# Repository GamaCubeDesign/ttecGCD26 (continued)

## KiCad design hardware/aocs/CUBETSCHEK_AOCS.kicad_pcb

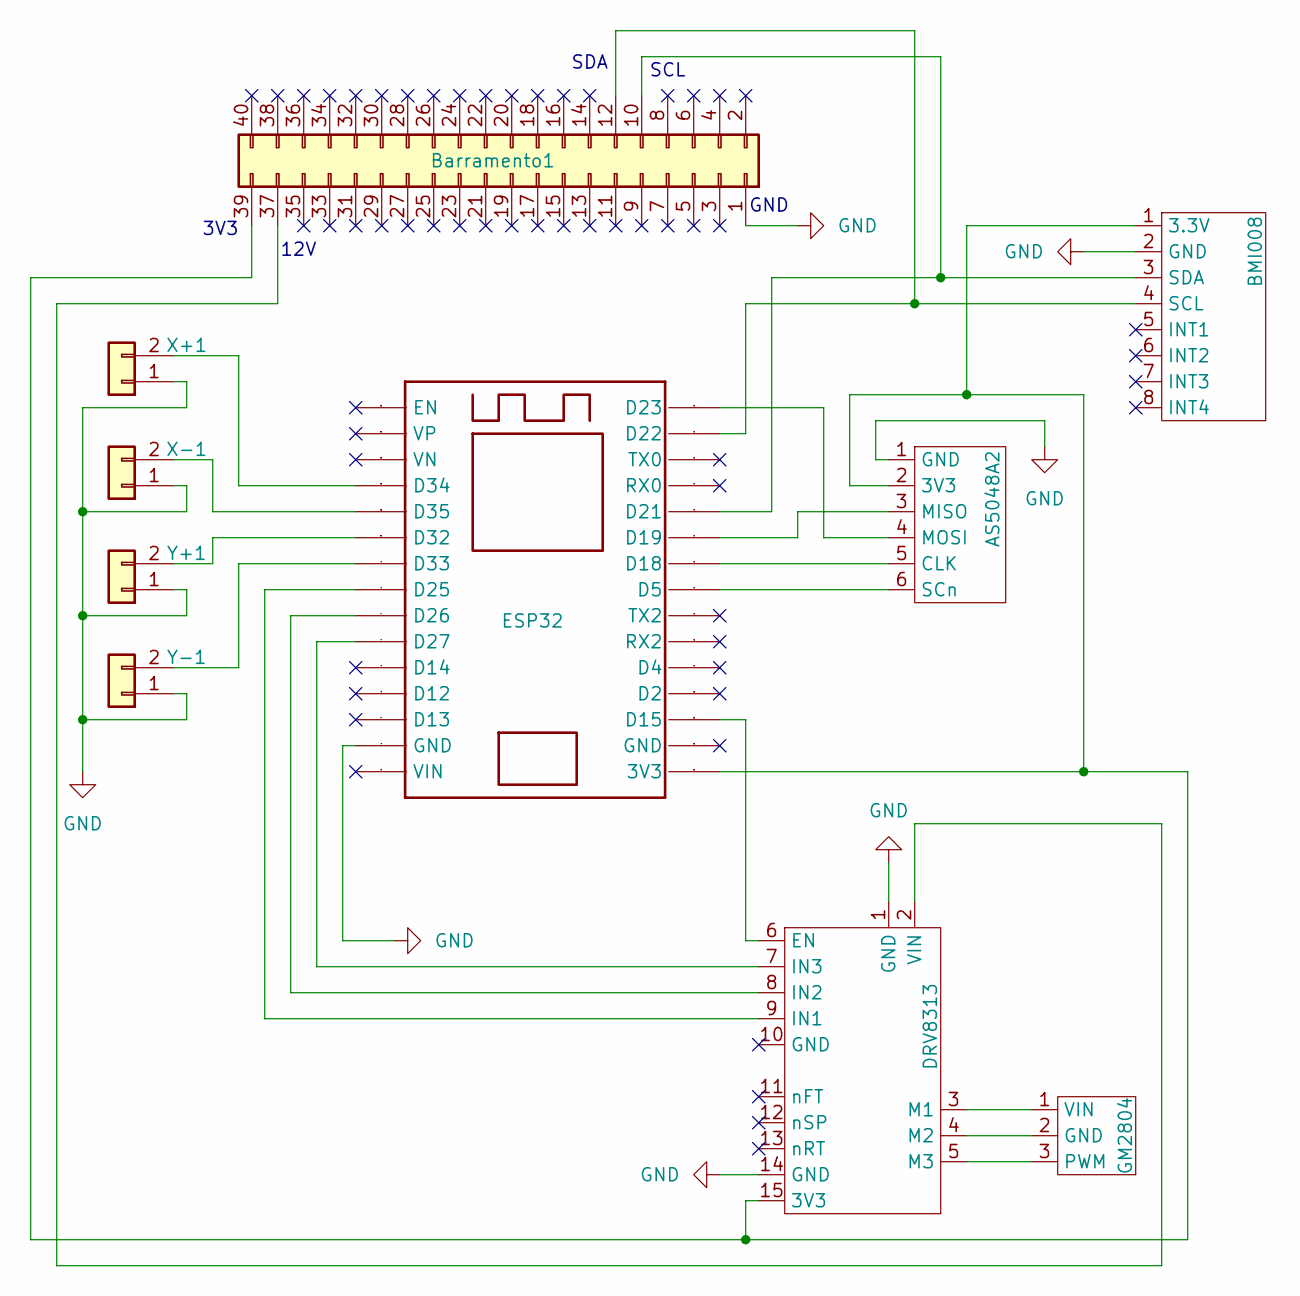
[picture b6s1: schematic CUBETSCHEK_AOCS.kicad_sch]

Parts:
AS5048A2: AS5048A
BMI008: BMI088
Barramento1: Barramento
DRV8313: DRV8313; DRV3813
ESP32: ESP32; ESP32-30p
GM2804: GM2804; GM2804_Molex_KK-3p-254
X+1: JST; JST_PLACA
X-1: JST; JST_PLACA
Y+1: JST; JST_PLACA
Y-1: JST; JST_PLACA

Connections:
GND: AS5048A2.1 (GND), BMI008.2 (GND), Barramento1.1, DRV8313.1 (GND), DRV8313.14 (GND), ESP32.2 (GND), X+1.1, X-1.1, Y+1.1, Y-1.1
unnamed: AS5048A2.2 (3V3), BMI008.1 (3.3V), Barramento1.39, DRV8313.15 (3V3), ESP32.16 (3V3)
unnamed: AS5048A2.5 (CLK), ESP32.24 (D18)
unnamed: AS5048A2.3 (MISO), ESP32.25 (D19)
unnamed: AS5048A2.4 (MOSI), ESP32.30 (D23)
unnamed: AS5048A2.6 (SCn), ESP32.23 (D5)
unnamed: BMI008.4 (SCL), Barramento1.12, ESP32.29 (D22)
unnamed: BMI008.3 (SDA), Barramento1.10, ESP32.26 (D21)
unnamed: Barramento1.37, DRV8313.2 (VIN)
unnamed: DRV8313.6 (EN), ESP32.18 (D15)
unnamed: DRV8313.9 (IN1), ESP32.8 (D25)
unnamed: DRV8313.8 (IN2), ESP32.7 (D26)
unnamed: DRV8313.7 (IN3), ESP32.6 (D27)
unnamed: DRV8313.3 (M1), GM2804.1 (VIN)
unnamed: DRV8313.4 (M2), GM2804.2 (GND)
unnamed: DRV8313.5 (M3), GM2804.3 (PWM)
unnamed: ESP32.10 (D32), Y+1.2
unnamed: ESP32.9 (D33), Y-1.2
unnamed: ESP32.12 (D34), X+1.2
unnamed: ESP32.11 (D35), X-1.2

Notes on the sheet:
GND
SDA
SCL
3V3
12V

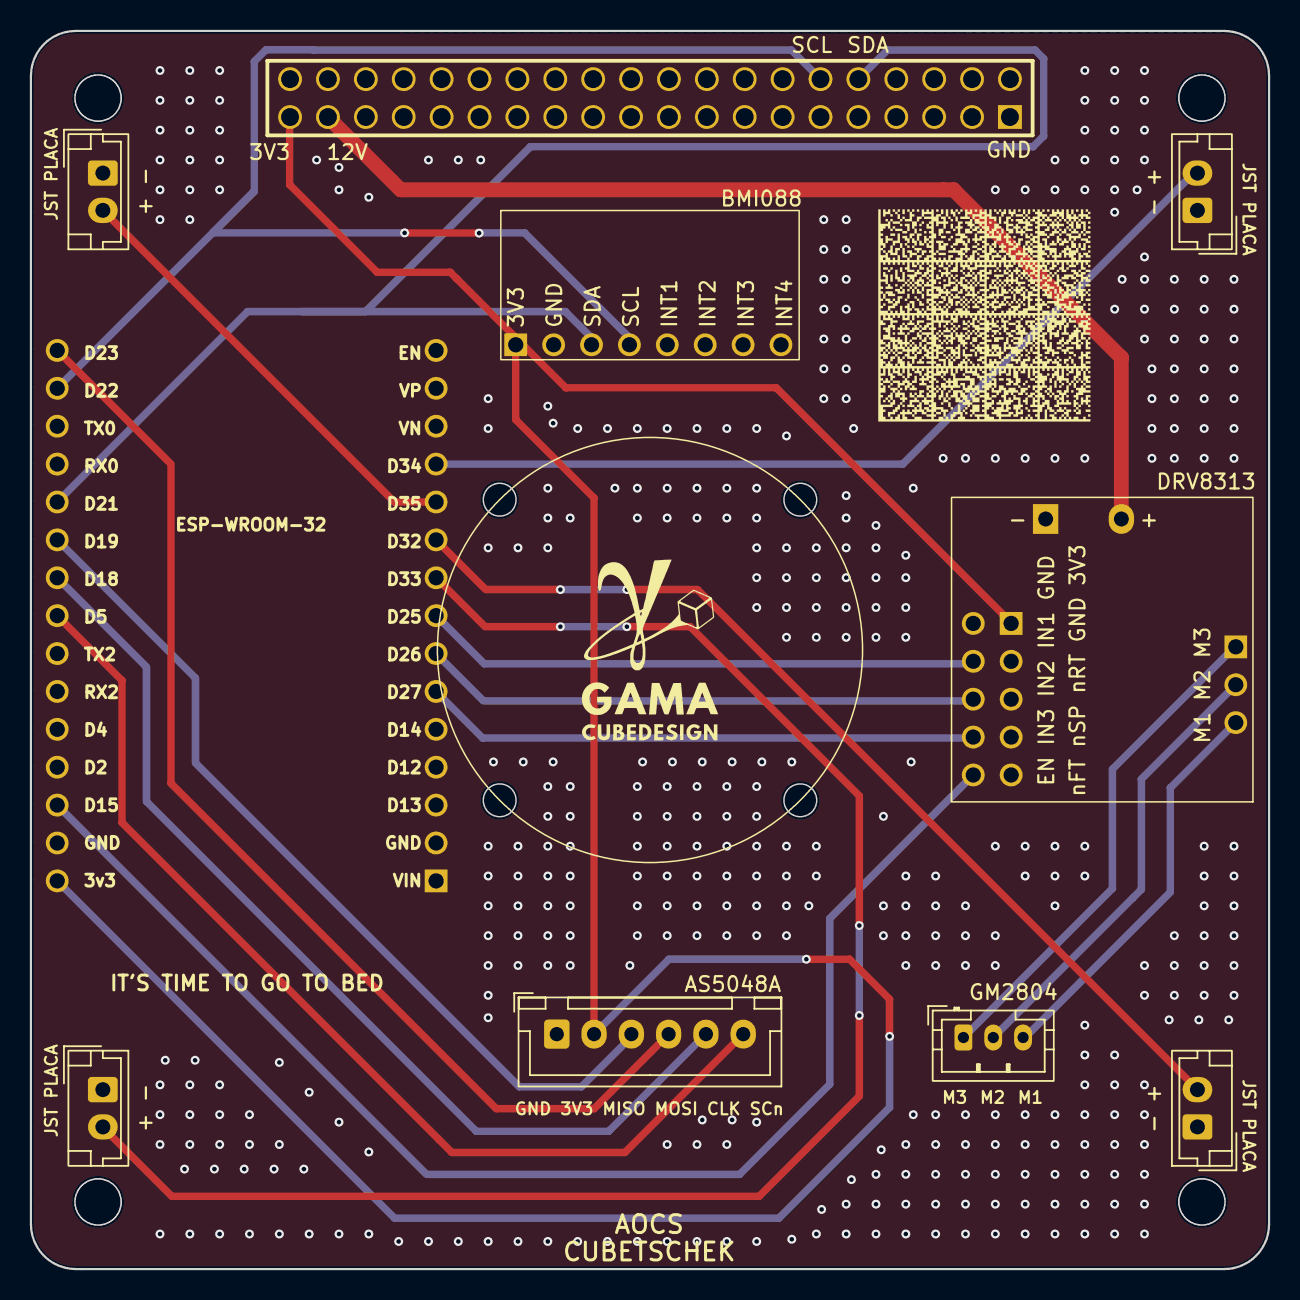
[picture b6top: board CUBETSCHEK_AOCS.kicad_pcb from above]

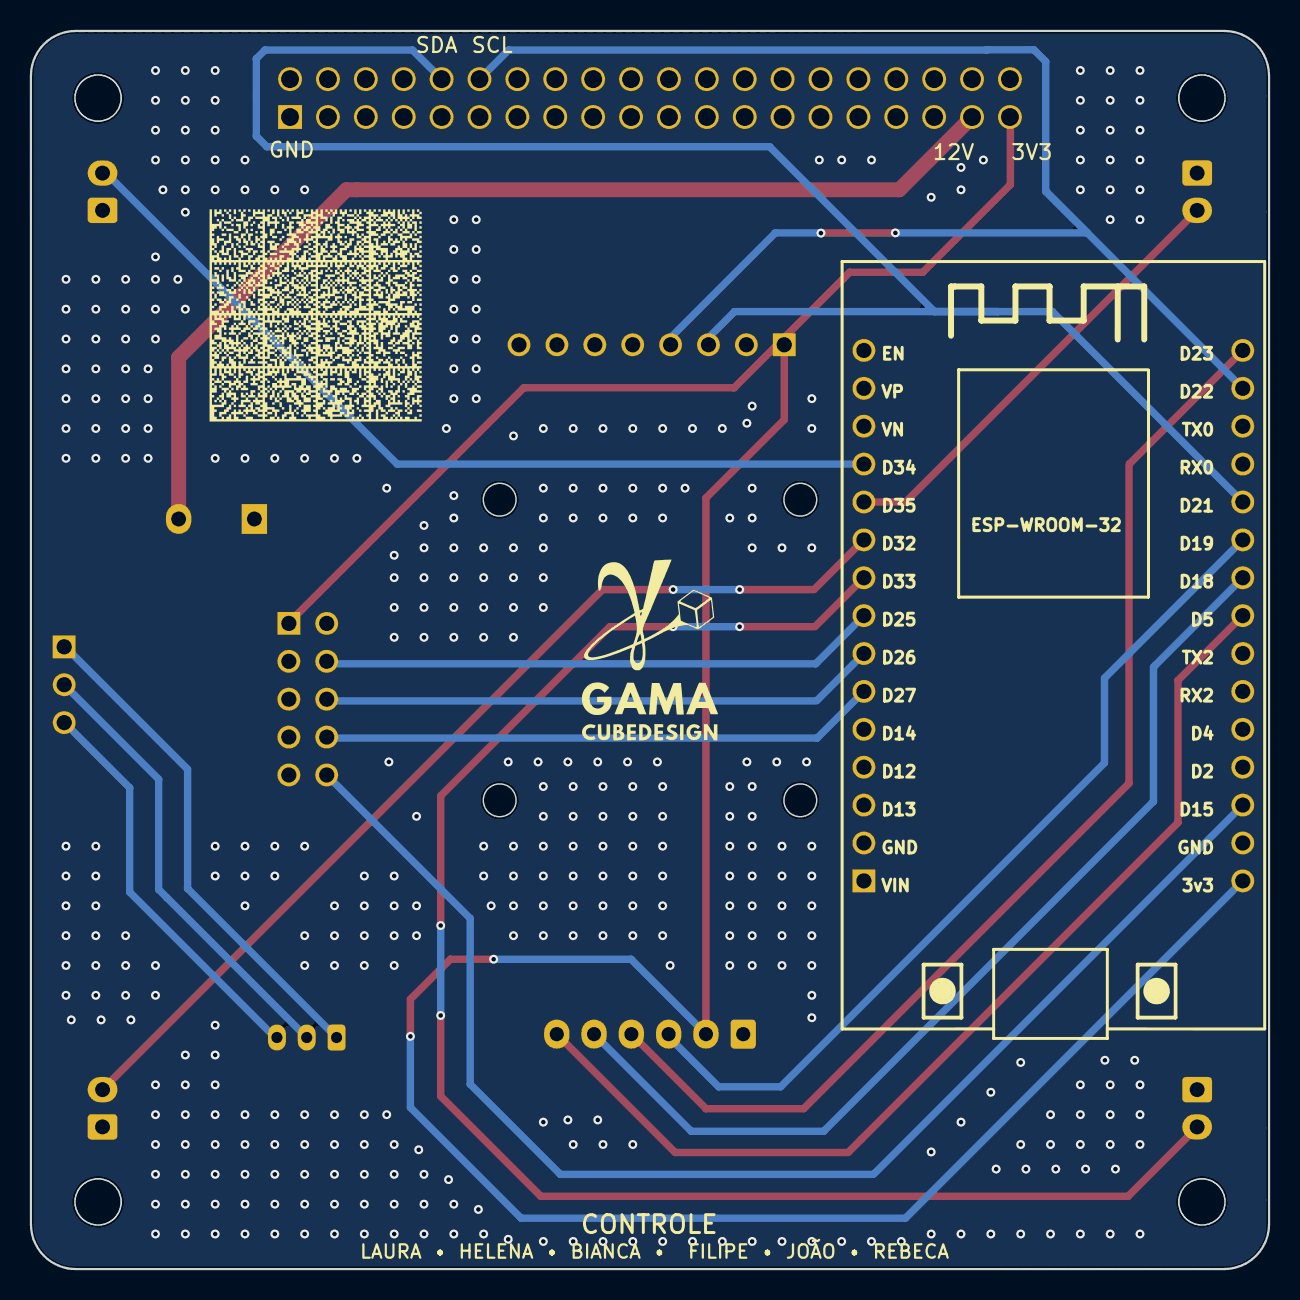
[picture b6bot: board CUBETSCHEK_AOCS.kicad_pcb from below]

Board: 2 copper layers, 83.0 x 83.0 mm, 12 parts (2 on the bottom side), 20 nets.

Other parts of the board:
logo: LOGO; logo
logo#2: LOGO; logo

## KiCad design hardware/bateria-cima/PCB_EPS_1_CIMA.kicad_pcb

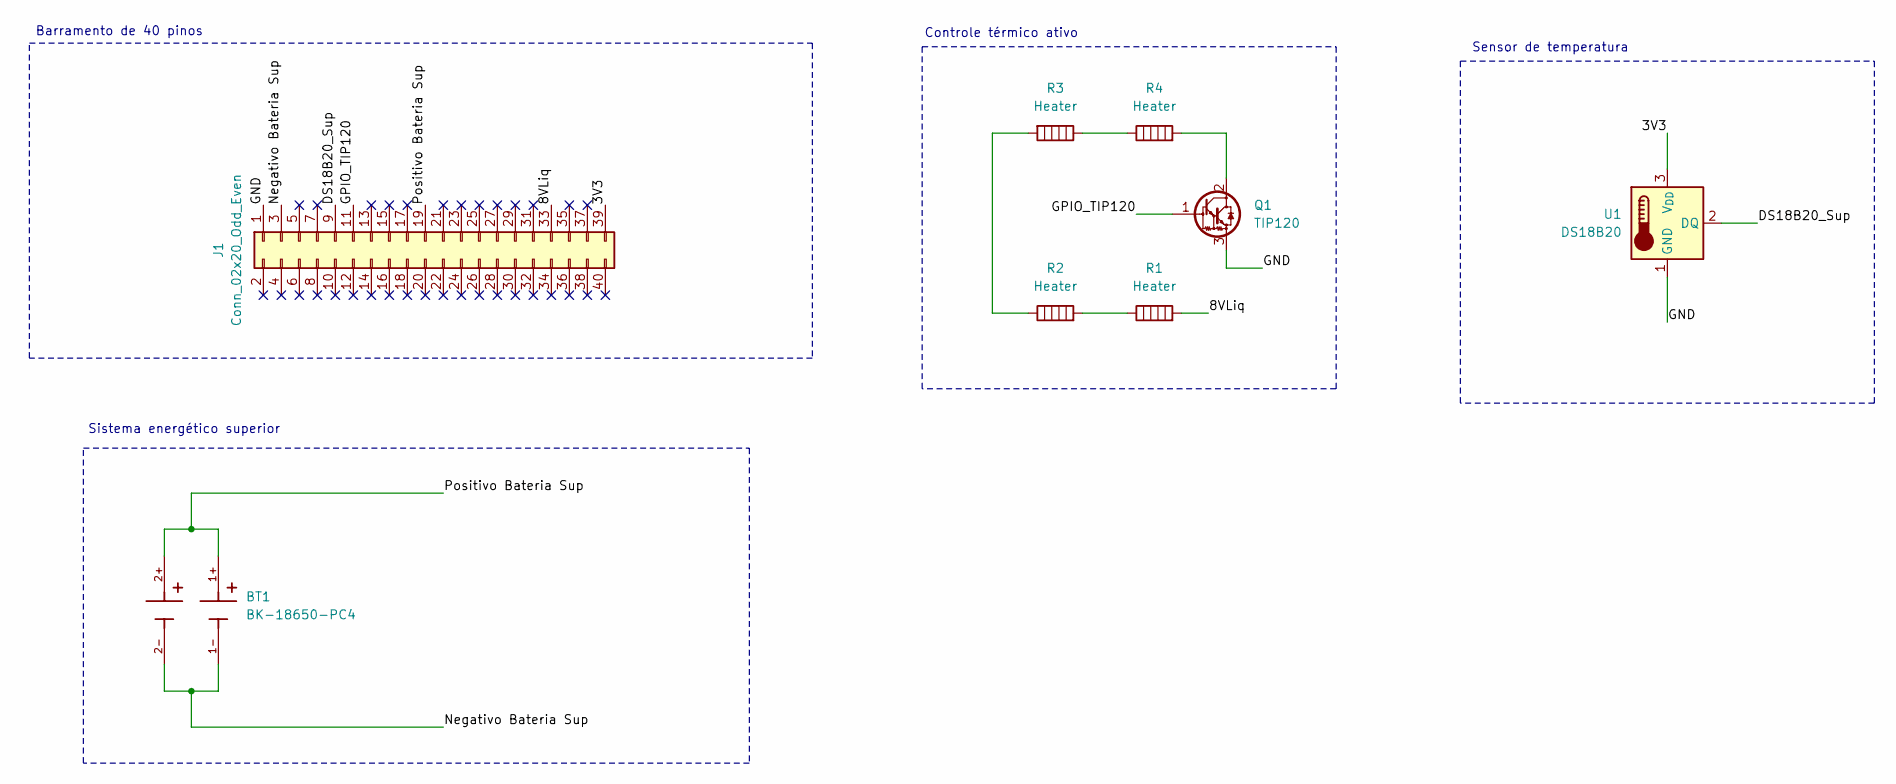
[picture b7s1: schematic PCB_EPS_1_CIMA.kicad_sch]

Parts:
BT1: BK-18650-PC4; BAT_BK-18650-PC4; PARTREV K
J1: Conn_02x20_Odd_Even; PC104_PSTD-2.54-2X20P
Q1: TIP120; TO-220-3_Vertical
R1, R2, R3, R4: Heater; R_Axial_DIN0922_L20.0mm_D9.0mm_P25.40mm_Horizontal
U1: DS18B20; TO-92_Inline

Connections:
/3V3: J1.39, U1.3 (V_{DD})
/8VLiq: J1.33, R1.2
/DS18B20_Sup: J1.9, U1.2 (DQ)
/GND: J1.1, Q1.3 (E), U1.1 (GND)
/GPIO_TIP120: J1.11, Q1.1 (B)
/Negativo Bateria Sup: BT1.1-, BT1.2-, J1.3
/Positivo Bateria Sup: BT1.1+, BT1.2+, J1.19
unnamed: Q1.2 (C), R4.2
unnamed: R1.1, R2.2
unnamed: R2.1, R3.2
unnamed: R3.1, R4.1

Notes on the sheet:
Controle térmico ativo
Sistema energético superior
Barramento de 40 pinos
Sensor de temperatura

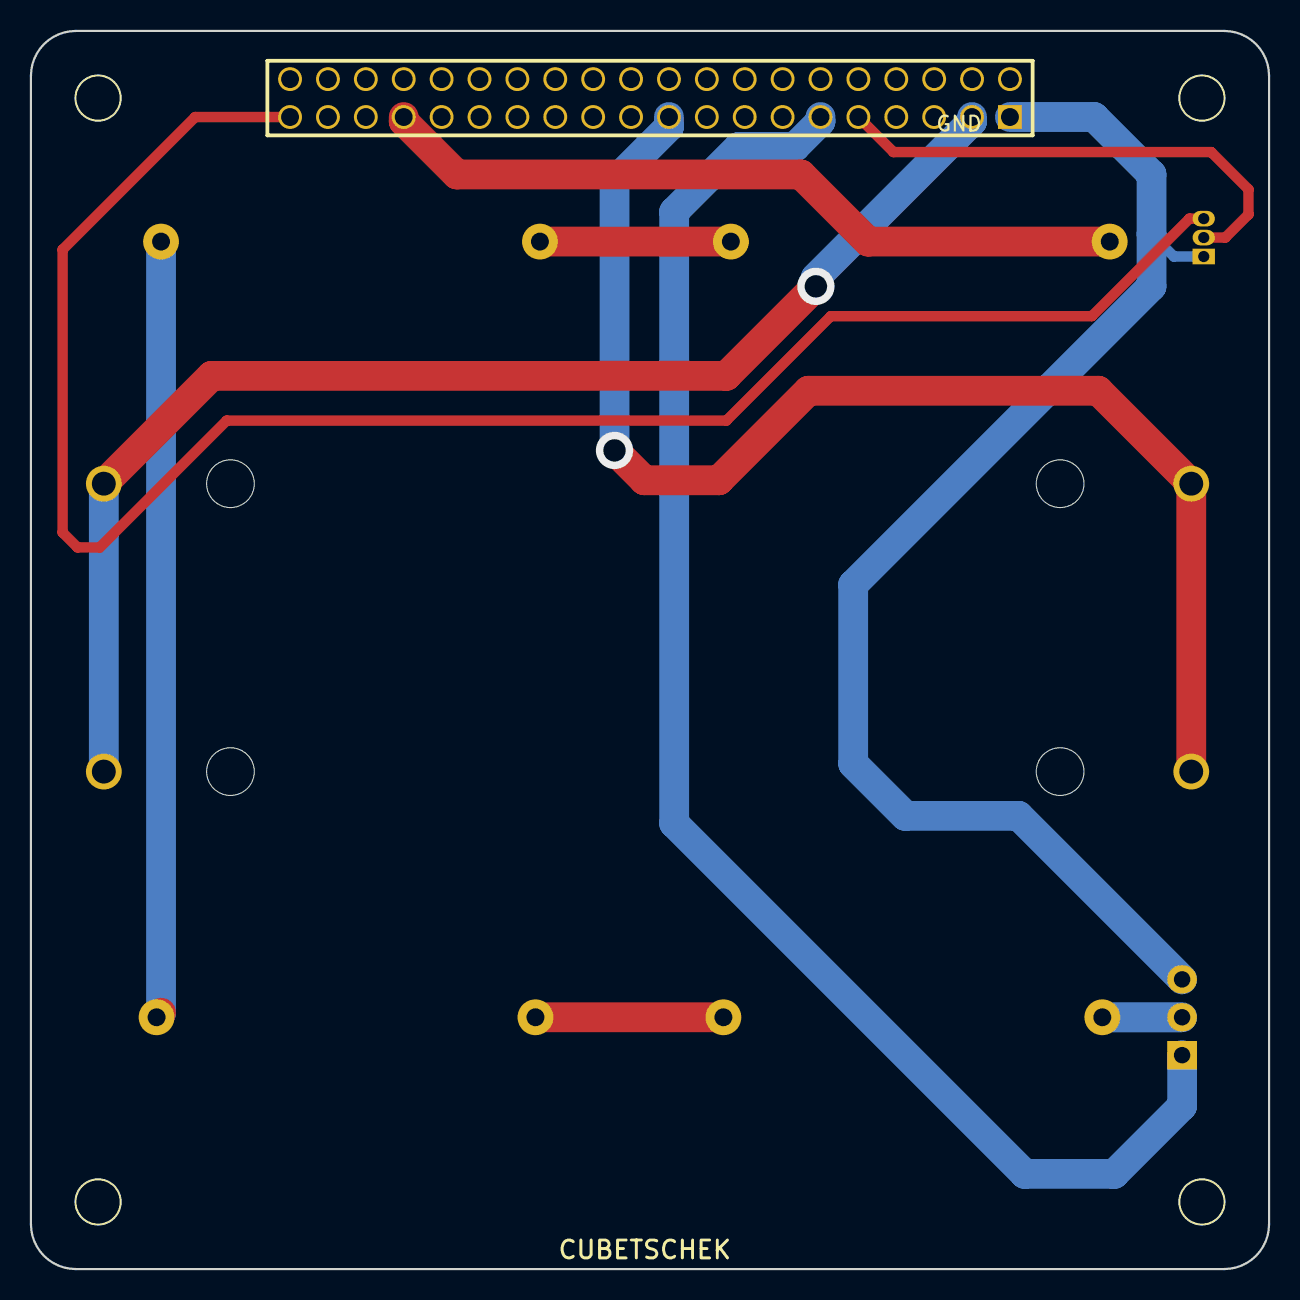
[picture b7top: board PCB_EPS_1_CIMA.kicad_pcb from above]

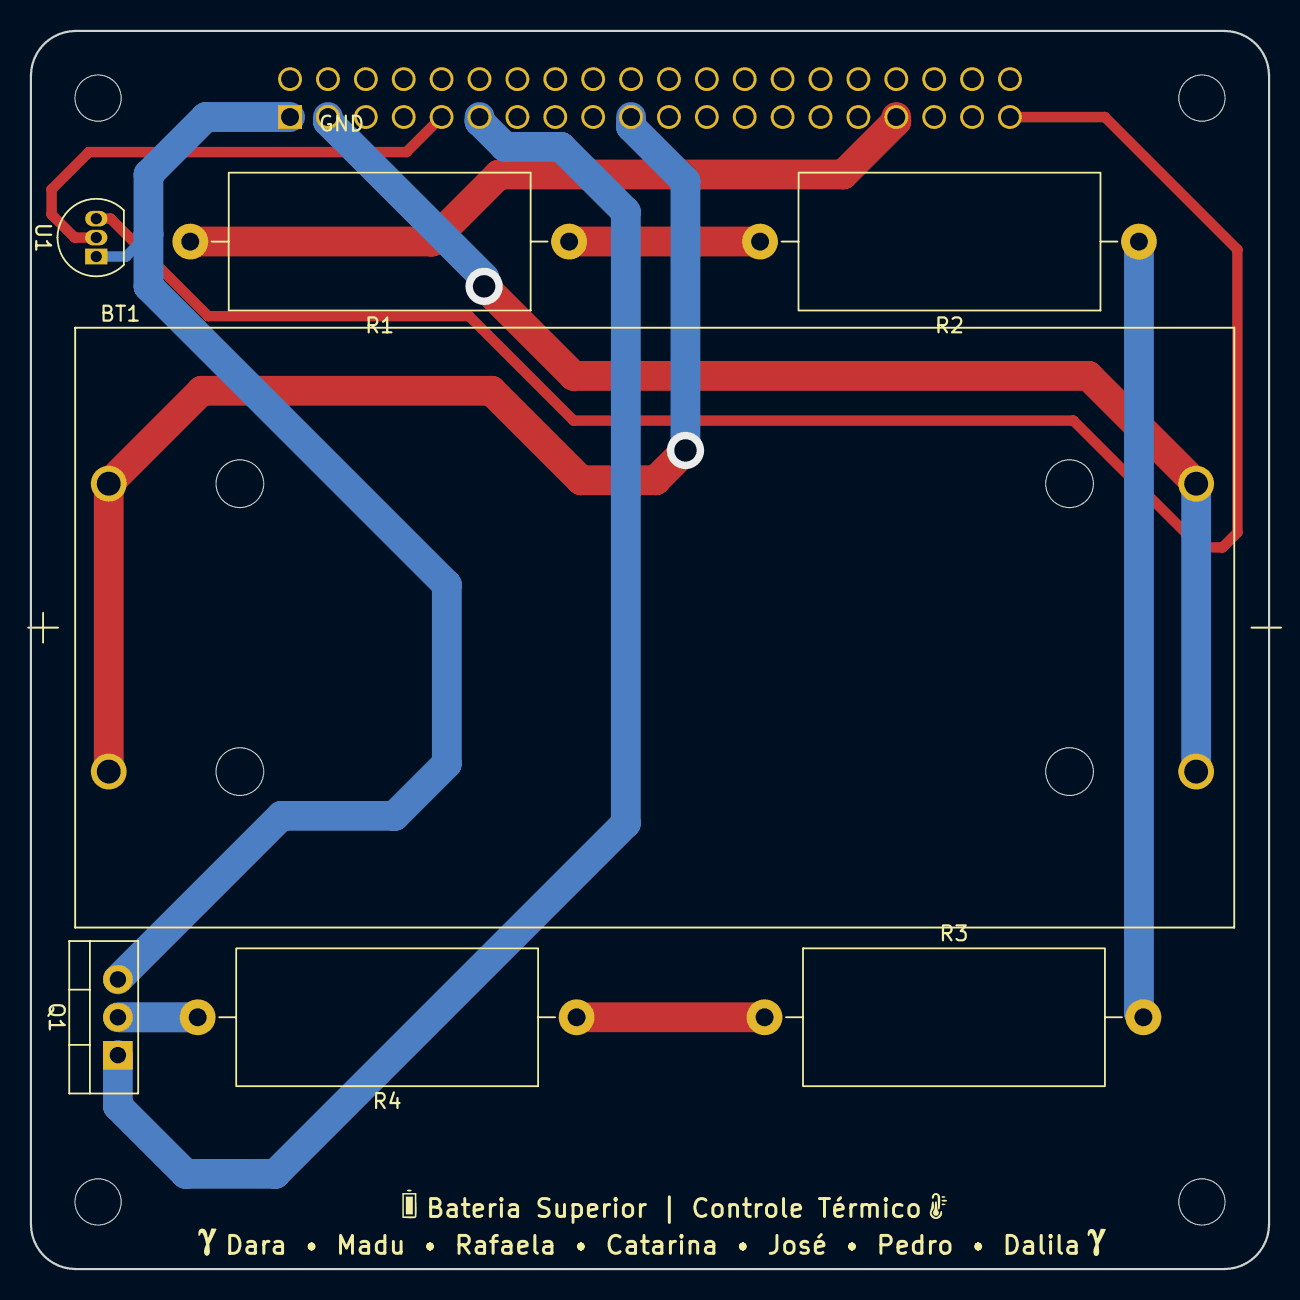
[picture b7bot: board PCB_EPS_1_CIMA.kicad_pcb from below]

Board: 2 copper layers, 83.0 x 83.0 mm, 8 parts (7 on the bottom side), 11 nets.

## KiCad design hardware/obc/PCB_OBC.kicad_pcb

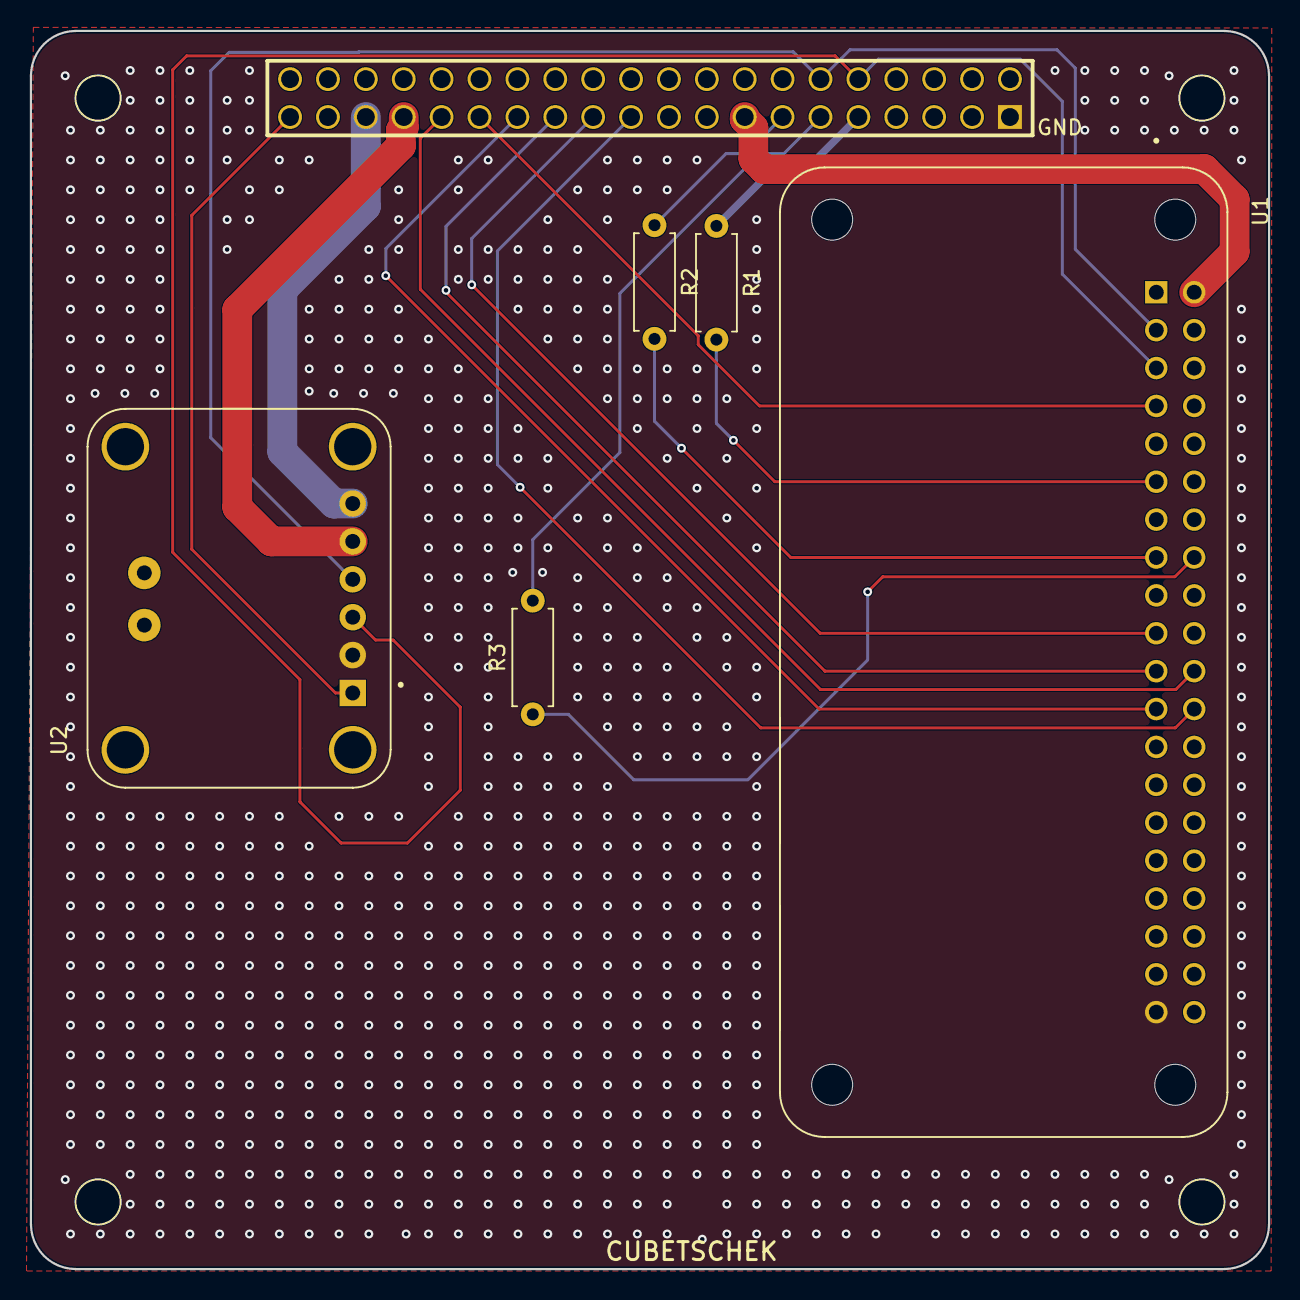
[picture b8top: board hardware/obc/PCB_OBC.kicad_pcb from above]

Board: 2 copper layers, 83.0 x 83.0 mm, 6 parts (0 on the bottom side), 19 nets.

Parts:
J1: PC104_PSTD-2.54-2X20P
R1, R2, R3: 4.7k; R_Axial_DIN0207_L6.3mm_D2.5mm_P7.62mm_Horizontal
U1: RASPBERRY_PI_ZERO_2_W; MODULE_RASPBERRY_PI_ZERO_2_W
U2: INA219; MODULE_INA219

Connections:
/3V3: J1.39, U2.1 (VCC)
/5V: J1.15, U1.2 (5V_2)
/8V Bruto: J1.35, U2.6 (VIN+)
/8V(INA): J1.33, U2.5 (VIN-)
/DIO0 LORA: J1.29, U1.7 (GPIO4/GPIO_GCLK)
/DS18B20: J1.9, R1.1
/GND: J1.1, U1.39 (GND_39), U2.2 (GND)
/MISO LORA: J1.25, U1.21 (GPIO9/SPI_MISO)
/MOSI LORA: J1.23, U1.19 (GPIO10/SPI_MOSI)
/NSS LORA: J1.21, U1.24 (GPIO8/SPI_~CE0)
/RESET LORA: J1.31, U1.22 (GPIO25/GPIO_GEN6)
/SCK LORA: J1.27, U1.23 (GPIO11/SPI_SCLK)
/SCL: J1.10, U1.5 (GPIO3/SCL), U2.3 (SCL)
/SDA: J1.12, U1.3 (GPIO2/SDA1), U2.4 (SDA)
/TIP120(CT): J1.11, R3.2
/TIP120(Mec): J1.13, R2.1
unnamed: R1.2, U1.11 (GPIO17/GPIO_GEN0)
unnamed: R2.2, U1.15 (GPIO22/GPIO_GEN3)
unnamed: R3.1, U1.16 (GPIO23/GPIO_GEN4)

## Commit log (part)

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2026-04-28 feat: adiciona estrutura inicial do sistema de telemetria
2026-05-13 feat: adiciona arquivos do sistema de telemetria e do sistema de relatórios
